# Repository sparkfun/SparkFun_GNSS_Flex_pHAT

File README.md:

SparkFun GNSS Flex pHAT
========================================

[*SparkFun GNSS Flex pHAT (GPS-28137)*](https://www.sparkfun.com/sparkfun-gnss-flex-phat.html)

The [SparkFun GNSS Flex pHAT](https://www.sparkfun.com/sparkfun-gnss-flex-phat.html) is a Raspberry Pi pHAT that functions as a *carrier board* for our SparkPNT GNSS Flex modules. With pre-soldered headers, no soldering is required to stack the pHAT on the headers of a Raspberry Pi, NVIDIA Jetson Nano, Google Coral, or other single-board computer with a similar 40-pin header.

The GNSS Flex pHAT also comes populated with two sets of 2x10 pin, 2mm pitch male headers for attaching a GNSS Flex module. With these headers, the GNSS Flex system is designed to be modular so that boards are pin-compatible for upgrades and can be easily swapped for repairs. Depending on the capabilities of the GNSS Flex module that is connected, these pins will breakout the USB, UART (x4), I<sup>2</sup>C, and SD card interfaces for the GNSS receiver along with any PPS or event signals, using a standardized pin out.

> [!NOTE]
> By default, we use the Raspberry Pi's primary serial bus *(i.e. **TX:** `GPIO14`/Pin `8`; **RX:** `GPIO15`/Pin `9`)* to communicate with the GNSS receiver of the SparkPNT GNSS Flex module. However, users can also utilize any of the other interfaces.

> [!IMPORTANT]
> Depending on the GNSS Flex module, this product will likely require an external antenna:
>
> - Be sure to check out the hookup guide for more information on the GNSS Flex module.
> - Users can also find [GNSS Antennas](https://www.sparkfun.com/gnss/gnss-antennas.html) in our catalog.
>
> Users will have two options for connecting an external GNSS antenna to their GNSS receiver.
>
> - The GNSS Flex modules will usually come with a U.FL connector for external antenna.
> - For a sturdier connection, an SMA connector is available on the SparkFun GNSS Flex pHAT that is bridged to an U.FL connector. Users simply need to jumper the U.FL connectors on both the SparkPNT GNSS Flex module and SparkFun GNSS Flex pHAT with a short U.FL cable.

> [!TIP]
> The SparkFun GNSS Flex pHAT has been tested and verified on the following platforms:
> - [Raspberry Pi](https://www.sparkfun.com/development-boards/single-board-computers/raspberry-pi/raspberry-pi-boards.html): 3B, 3B+, 3A+, Zero 2W, 4B, 5B
> - [NVidia Jetson Orin Nano](https://www.sparkfun.com/nvidia-jetson-orin-nano-developer-kit.html)

Documentation
--------------
- **[Hookup Guide (mkdocs)](http://docs.sparkfun.com/SparkFun_GNSS_Flex_System/)** - A hookup guide for the entire ecosystem of SparkFun GNSS Flex carrier boards and SparkPNT GNSS Flex modules, hosted by GitHub pages.<br>

Repository Contents
-------------------
- **[/docs](/docs/)** - Online documentation files
  - [/assets](/docs/assets/) - Assets files
    - [/3d_model](/docs/assets/3d_model/) - Files for the 3D models
      - [/3D CAD Model](/docs/assets/3d_model/cad_model.step) (.step)
    - [/board_files](/docs/assets/board_files/) - Files for the product design
      - [KiCad Design Files](/docs/assets/board_files/kicad_files.zip) (.zip)
      - [Schematic](/docs/assets/board_files/schematic.pdf) (.pdf)
      - [Dimensions](/docs/assets/board_files/dimensions.pdf) (.pdf)
    - [/component_documentation](/docs/assets/component_documentation/) - Datasheets for hardware components
    - [/img/hookup_guide/](/docs/assets/img/hookup_guide/) - Images for hookup guide documentation
- **[/Hardware](/Hardware/)** - Hardware design files (.brd, .sch)
  - **[/Production](/Production/)** - Production files

Product Variants
----------------
GNSS Flex *Carrier* Boards:
- [GPS-28962](https://www.sparkfun.com/sparkfun-gnss-flex-breakout.html) - GNSS Flex Breakout
- [GPS-28137](https://www.sparkfun.com/sparkfun-gnss-flex-phat.html) - GNSS Flex pHAT *(only)*

- GNSS Flex pHAT Kits:
  - pHAT + GNSS Module *(only)*:
    - [GPS-28766](https://www.sparkfun.com/sparkfun-gnss-flex-phat-mosaic-x5.html) - w/ the Septentrio mosaic-X5 GNSS Flex module
    - [GPS-28929](https://www.sparkfun.com/sparkfun-gnss-flex-phat-lg290p.html) - w/ the Quectel LG290P GNSS Flex module
    - [GPS-29491](https://www.sparkfun.com/sparkfun-gnss-flex-phat-dan-f10n.html) - w/ the u-blox DAN-F10N GNSS Flex module
    - [GPS-29887](https://www.sparkfun.com/sparkfun-gnss-flex-phat-zed-x20p.html) - w/ the u-blox ZED-X20P GNSS Flex module
    - [GPS-29890](https://www.sparkfun.com/sparkfun-gnss-flex-phat-lg580p.html) - w/ the Quectel LG580P GNSS Flex module
  - pHAT + GNSS Module w/ IMU:
    - [GPS-29891](https://www.sparkfun.com/sparkfun-gnss-flex-phat-lg290p-im19-imu.html) - w/ the Quectel LG290P GNSS Flex module + IM19 IMU
    - [GPS-29888](https://www.sparkfun.com/sparkfun-gnss-flex-phat-zed-x20p-im19-imu.html) - w/ the u-blox ZED-X20P GNSS Flex module + IM19 IMU

Version History
---------------
- [v01](https://github.com/sparkfun/SparkFun_GNSS_Flex_pHAT/releases/tag/v01) - Initial Release
- [v02](https://github.com/sparkfun/SparkFun_GNSS_Flex_pHAT/releases/tag/v02) - Adds DAN-F10N GNSS Flex module
- [v03](https://github.com/sparkfun/SparkFun_GNSS_Flex_pHAT/releases/tag/v03) - Adds LG290P and ZED-X20P GNSS Flex modules w/ optional IM19 IMU
- [v04](https://github.com/sparkfun/SparkFun_GNSS_Flex_pHAT/releases/tag/v04) - Update docs and link GNSS Flex breakout board
- [v10](https://github.com/sparkfun/SparkFun_GNSS_Flex_pHAT/releases/tag/v10) - Refactored the 3D model for new color adjustment script and linked the LG580P GNSS Flex module

License Information
-------------------

This product is ***open source***!

Please review the [`LICENSE.md`](./LICENSE.md) file for license information.

If you have any questions or concerns about licensing, please contact technical support on our [SparkFun forums](https://community.sparkpnt.com).

Distributed as-is; no warranty is given.

- Your friends at SparkFun.

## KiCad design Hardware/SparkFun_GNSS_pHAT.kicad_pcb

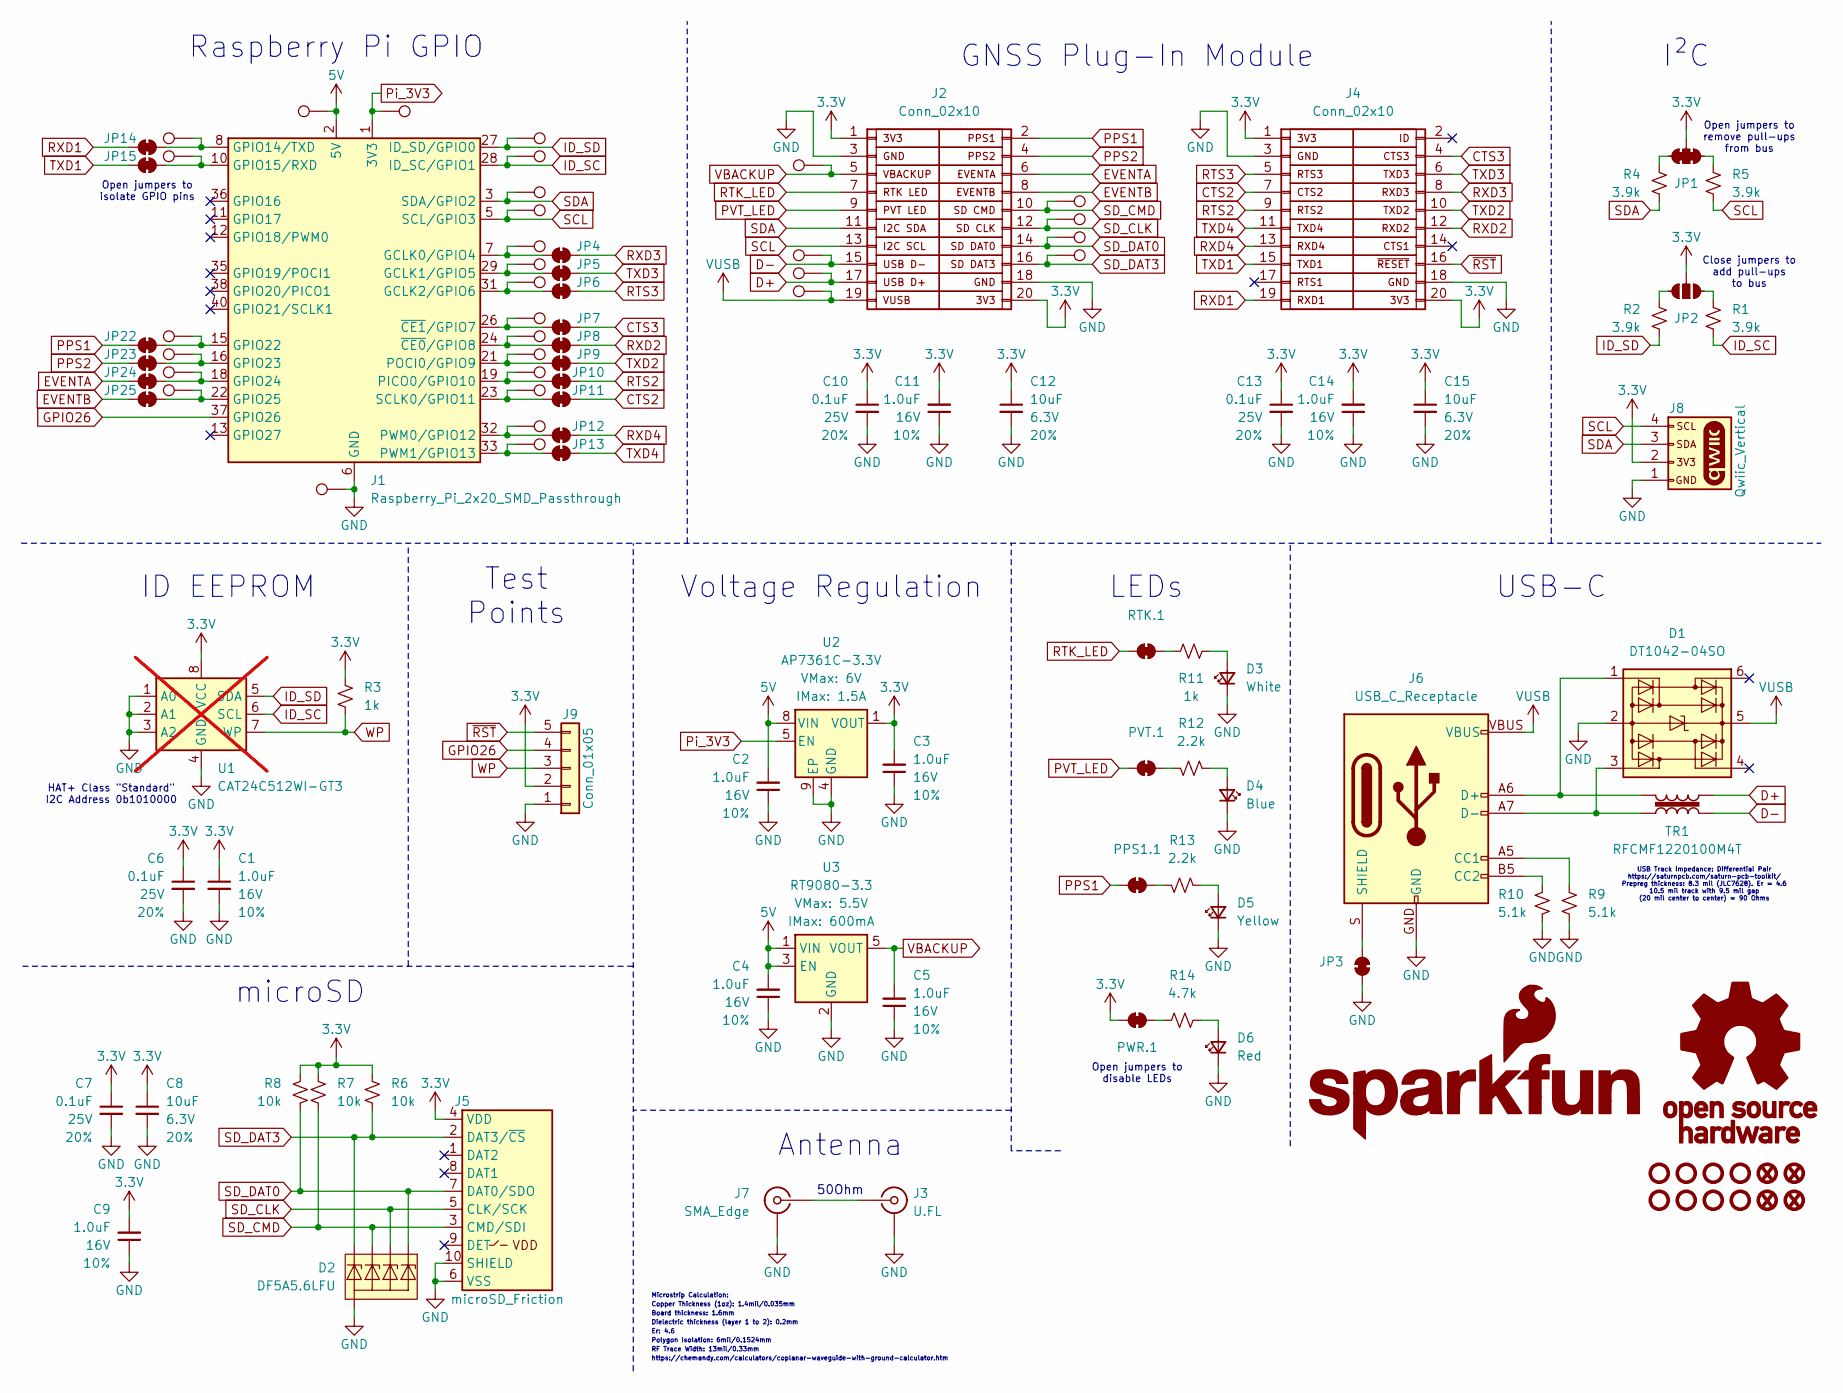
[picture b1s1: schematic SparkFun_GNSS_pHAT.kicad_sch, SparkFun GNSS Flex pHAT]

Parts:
C1, C2, C3, C4, C5, C9, C11, C14: 1.0uF; C_0603_1608Metric; Voltage 16V; Tolerance 10%
C6, C7, C10, C13: 0.1uF; C_0603_1608Metric; Voltage 25V; Tolerance 20%
C8, C12, C15: 10uF; C_0603_1608Metric; Voltage 6.3V; Tolerance 20%
D1: DT1042-04SO; SOT23-6
D2: DF5A5.6LFU; SOT-353
D3: White; LED_0603_1608Metric_White
D4: Blue; LED_0603_1608Metric_Blue
D5: Yellow; LED_0603_1608Metric_Yellow
D6: Red; LED_0603_1608Metric_Red
FID1, FID2, FID3, FID4: Fiducial_0.5mm; Fiducial_0.5mm_Mask1mm
G1: SparkFun_Logo
G3: OSHW_Logo; Creative_Commons_License
J1: Raspberry_Pi_2x20_SMD_Passthrough; Raspberry_Pi_Shield_Top_Entry_No_Mounting_Holes
J2, J4: Conn_02x10; 2x10_2.0mm_Male_Pins_Vertical_SMD_Pegs
J3: U.FL
J5: microSD_Friction; microSD_Friction_Fit_Common
J6: USB_C_Receptacle; USB-C_16
J7: SMA_Edge
J8: Qwiic_Vertical; JST_SMD_1.0mm-4_Vertical_Black
J9: Conn_01x05; 1x05
JP1: Jumper_3_NC-2_Trace
JP2: Jumper_3_NO
JP3, JP4, JP5, JP6, JP7, JP8, JP9, JP10, JP11, JP12, JP13, JP14, JP15, JP22, JP23, JP24, JP25: Jumper_2_NC_Trace
PPS1.1: Jumper_2_NC_Trace
PVT.1: Jumper_2_NC_Trace
PWR.1: Jumper_2_NC_Trace
R1, R2, R4, R5: 3.9k; R_0603_1608Metric
R3, R11: 1k; R_0603_1608Metric
R6, R7, R8: 10k; R_0603_1608Metric
R9, R10: 5.1k; R_0603_1608Metric
R12, R13: 2.2k; R_0603_1608Metric
R14: 4.7k; R_0603_1608Metric
RTK.1: Jumper_2_NC_Trace
ST1, ST2, ST3, ST4: Standoff
ST5, ST6, ST7, ST8: Standoff; Standoff_Hole-2.75mm_Clearance-1.625mm
TP1, TP2, TP3, TP4, TP5, TP6, TP7, TP8, TP9, TP10, TP11, TP12, TP13, TP14, TP15, TP16, TP17, TP18, TP19, TP20, TP21, TP22, TP23, TP24, TP25, TP26, TP27, TP28, TP29, TP30, TP31: 1.25mm; TestPoint-1.25mm
TR1: RFCMF1220100M4T
U1: CAT24C512WI-GT3; SO-8; not fitted
U2: AP7361C-3.3V; UDFN-8
U3: RT9080-3.3; SOT23-5

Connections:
3.3V: C1.1, C3.2, C6.1, C7.1, C8.1, C9.2, C10.1, C11.2, C12.1, C13.1, C14.2, C15.1, J2.1, J2.20, J4.1, J4.20, J5.4 (VDD), J8.2, J9.2, JP1.2 (B), JP2.2 (B), PWR.1.2 (B), R3.2, R6.2, R7.2, R8.2, U1.8 (VCC), U2.1 (VOUT)
5V: C2.2, C4.2, J1.2 (5V), J1.4 (5V), TP22.1, U2.8 (VIN), U3.1 (VIN), U3.3 (EN)
CTS2: J4.7, JP11.2 (B)
CTS3: J4.4, JP7.2 (B)
D+: J2.17, TP25.1, TR1.4
D-: J2.15, TP24.1, TR1.2
EVENTA: J2.6, JP24.1 (A)
EVENTB: J2.8, JP25.1 (A)
GND: C1.2, C2.1, C3.1, C4.1, C5.1, C6.2, C7.2, C8.2, C9.1, C10.2, C11.1, C12.2, C13.2, C14.1, C15.2, D1.2 (GND), D2.2 (A), D3.1 (K), D4.1 (K), D5.1 (K), D6.1 (K), J1.6 (GND), J1.9 (GND), J1.14 (GND), J1.20 (GND), J1.25 (GND), J1.30 (GND), J1.34 (GND), J1.39 (GND), J2.3, J2.18, J3.2 (Ext), J4.3, J4.18, J5.6 (VSS), J5.10 (SHIELD), J6.GND, J7.2 (Ext), J8.1, J9.1, JP3.1 (A), R9.1, R10.1, TP31.1, U1.1 (A0), U1.2 (A1), U1.3 (A2), U1.4 (GND), U2.4 (GND), U2.9 (EP), U3.2 (GND)
GPIO26: J1.37 (GPIO26), J9.4
ID_SC: J1.28 (ID_SC/GPIO1), R1.1, TP2.1, U1.6 (SCL)
ID_SD: J1.27 (ID_SD/GPIO0), R2.1, TP1.1, U1.5 (SDA)
unnamed: D1.1 (I/O1), J6.A6 (D+), J6.B6 (D+), TR1.3
unnamed: D1.3 (I/O2), J6.A7 (D-), J6.B7 (D-), TR1.1
unnamed: D3.2 (A), R11.1
unnamed: D4.2 (A), R12.1
unnamed: D5.2 (A), R13.1
unnamed: D6.2 (A), R14.2
unnamed: J1.7 (GCLK0/GPIO4), JP4.1 (A), TP5.1
unnamed: J1.29 (GCLK1/GPIO5), JP5.1 (A), TP6.1
unnamed: J1.31 (GCLK2/GPIO6), JP6.1 (A), TP7.1
unnamed: J1.8 (GPIO14/TXD), JP14.2 (B), TP15.1
unnamed: J1.10 (GPIO15/RXD), JP15.2 (B), TP16.1
unnamed: J1.15 (GPIO22), JP22.2 (B), TP17.1
unnamed: J1.16 (GPIO23), JP23.2 (B), TP18.1
unnamed: J1.18 (GPIO24), JP24.2 (B), TP19.1
unnamed: J1.22 (GPIO25), JP25.2 (B), TP20.1
unnamed: J1.19 (PICO0/GPIO10), JP10.1 (A), TP11.1
unnamed: J1.21 (POCI0/GPIO9), JP9.1 (A), TP10.1
unnamed: J1.32 (PWM0/GPIO12), JP12.1 (A), TP13.1
unnamed: J1.33 (PWM1/GPIO13), JP13.1 (A), TP14.1
unnamed: J1.23 (SCLK0/GPIO11), JP11.1 (A), TP12.1
unnamed: J1.24 (~CE0/GPIO8), JP8.1 (A), TP9.1
unnamed: J1.26 (~CE1/GPIO7), JP7.1 (A), TP8.1
unnamed: J3.1 (In), J7.1 (In)
unnamed: J6.A5 (CC1), R9.2
unnamed: J6.B5 (CC2), R10.2
unnamed: J6.S (SHIELD), JP3.2 (B)
unnamed: JP1.1 (A), R5.2
unnamed: JP1.3 (C), R4.2
unnamed: JP2.1 (A), R1.2
unnamed: JP2.3 (C), R2.2
unnamed: PPS1.1.2 (B), R13.2
unnamed: PVT.1.2 (B), R12.2
unnamed: PWR.1.1 (A), R14.1
unnamed: R11.2, RTK.1.2 (B)
PPS1: J2.2, JP22.1 (A), PPS1.1.1 (A)
PPS2: J2.4, JP23.1 (A)
PVT_LED: J2.9, PVT.1.1 (A)
Pi_3V3: J1.1 (3V3), J1.17 (3V3), TP23.1, U2.5 (EN)
RTK_LED: J2.7, RTK.1.1 (A)
RTS2: J4.9, JP10.2 (B)
RTS3: J4.5, JP6.2 (B)
RXD1: J4.19, JP14.1 (A)
RXD2: J4.12, JP8.2 (B)
RXD3: J4.8, JP4.2 (B)
RXD4: J4.13, JP12.2 (B)
SCL: J1.5 (SCL/GPIO3), J2.13, J8.4, R5.1, TP4.1
SDA: J1.3 (SDA/GPIO2), J2.11, J8.3, R4.1, TP3.1
SD_CLK: D2.3 (K2), J2.12, J5.5 (CLK/SCK), TP29.1
SD_CMD: D2.4 (K3), J2.10, J5.3 (CMD/SDI), R7.1, TP30.1
SD_DAT0: D2.1 (K1), J2.14, J5.7 (DAT0/SDO), R8.1, TP28.1
SD_DAT3: D2.5 (K4), J2.16, J5.2 (DAT3/~CS), R6.1, TP27.1
TXD1: J4.15, JP15.1 (A)
TXD2: J4.10, JP9.2 (B)
TXD3: J4.6, JP5.2 (B)
TXD4: J4.11, JP13.2 (B)
VBACKUP: C5.2, J2.5, TP21.1, U3.5 (VOUT)
VUSB: D1.5 (VCC), J2.19, J6.VBUS, TP26.1
WP: J9.3, R3.1, U1.7 (WP)
~RST: J4.16, J9.5

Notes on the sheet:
Er: 4.6
50Ohm
Raspberry Pi GPIO
Board thickness: 1.6mm
https://chemandy.com/calculators/coplanar-waveguide-with-ground-calculator.htm
Close jumpers to add pull-ups to bus
Open jumpers to remove pull-ups from bus
RF Trace Width: 13mil/0.33mm
Test Points
Polygon Isolation: 6mil/0.1524mm
microSD
Antenna
Open jumpers to disable LEDs
Dielectric thickness (layer 1 to 2): 0.2mm
LEDs
Voltage Regulation
USB Track Impedance: Differential Pair https://saturnpcb.com/saturn-pcb-toolkit/ Prepreg thickness: 8.3 mil (JLC7628). Er = 4.6 10.5 mil track with 9.5 mil gap (20 mil center to center) = 90 Ohms
Open jumpers to isolate GPIO pins
ID EEPROM
HAT+ Class "Standard" I2C Address 0b1010000
GNSS Plug-In Module
Microstrip Calculation:
I²C
USB-C
Copper Thickness (1oz): 1.4mil/0.035mm

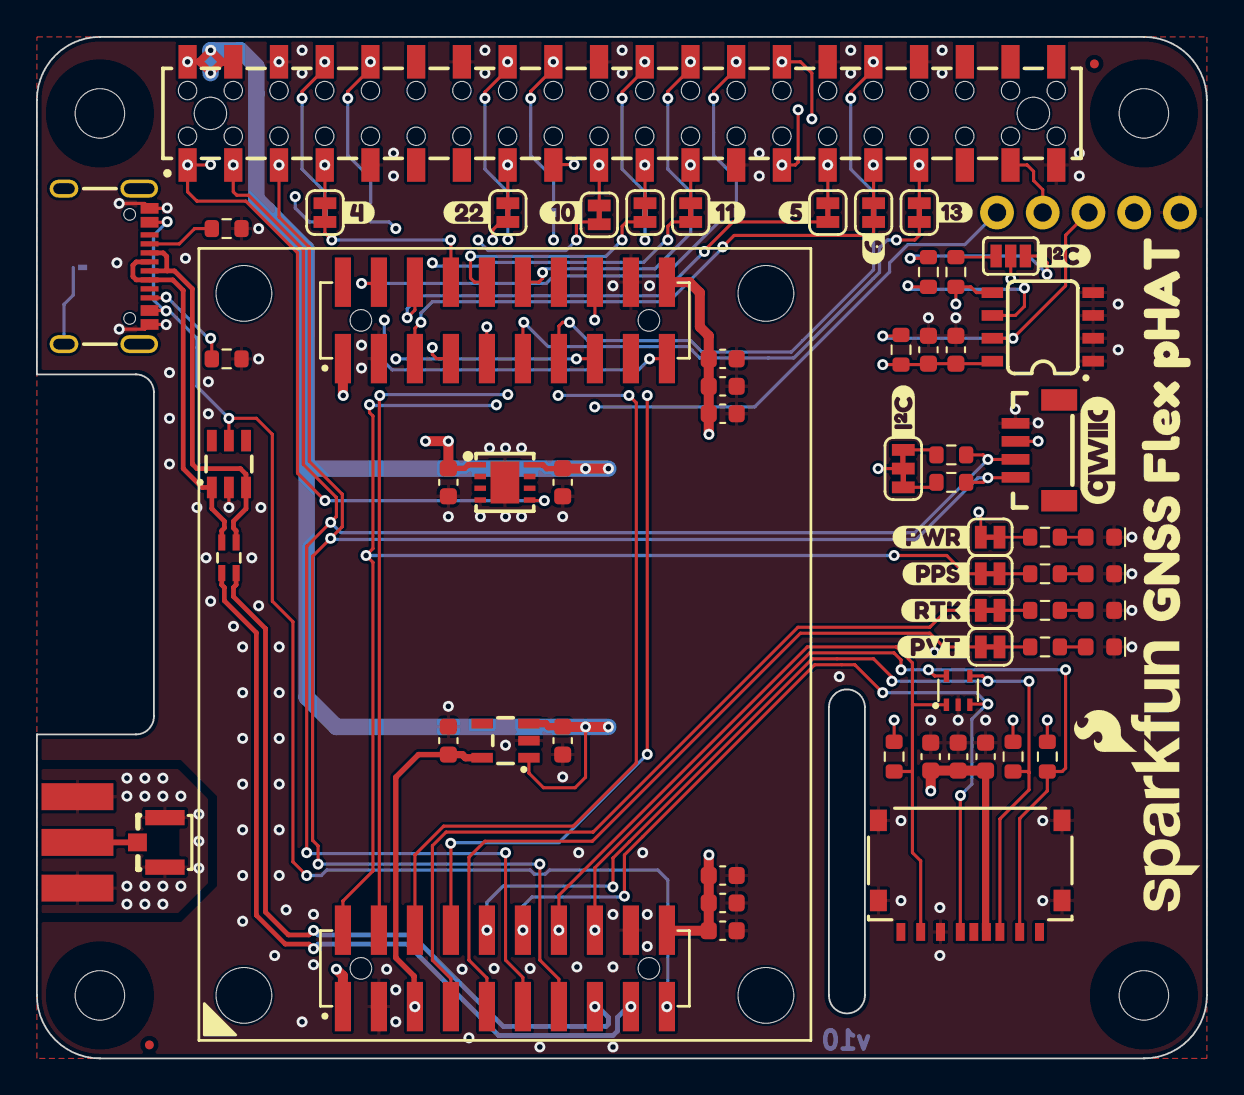
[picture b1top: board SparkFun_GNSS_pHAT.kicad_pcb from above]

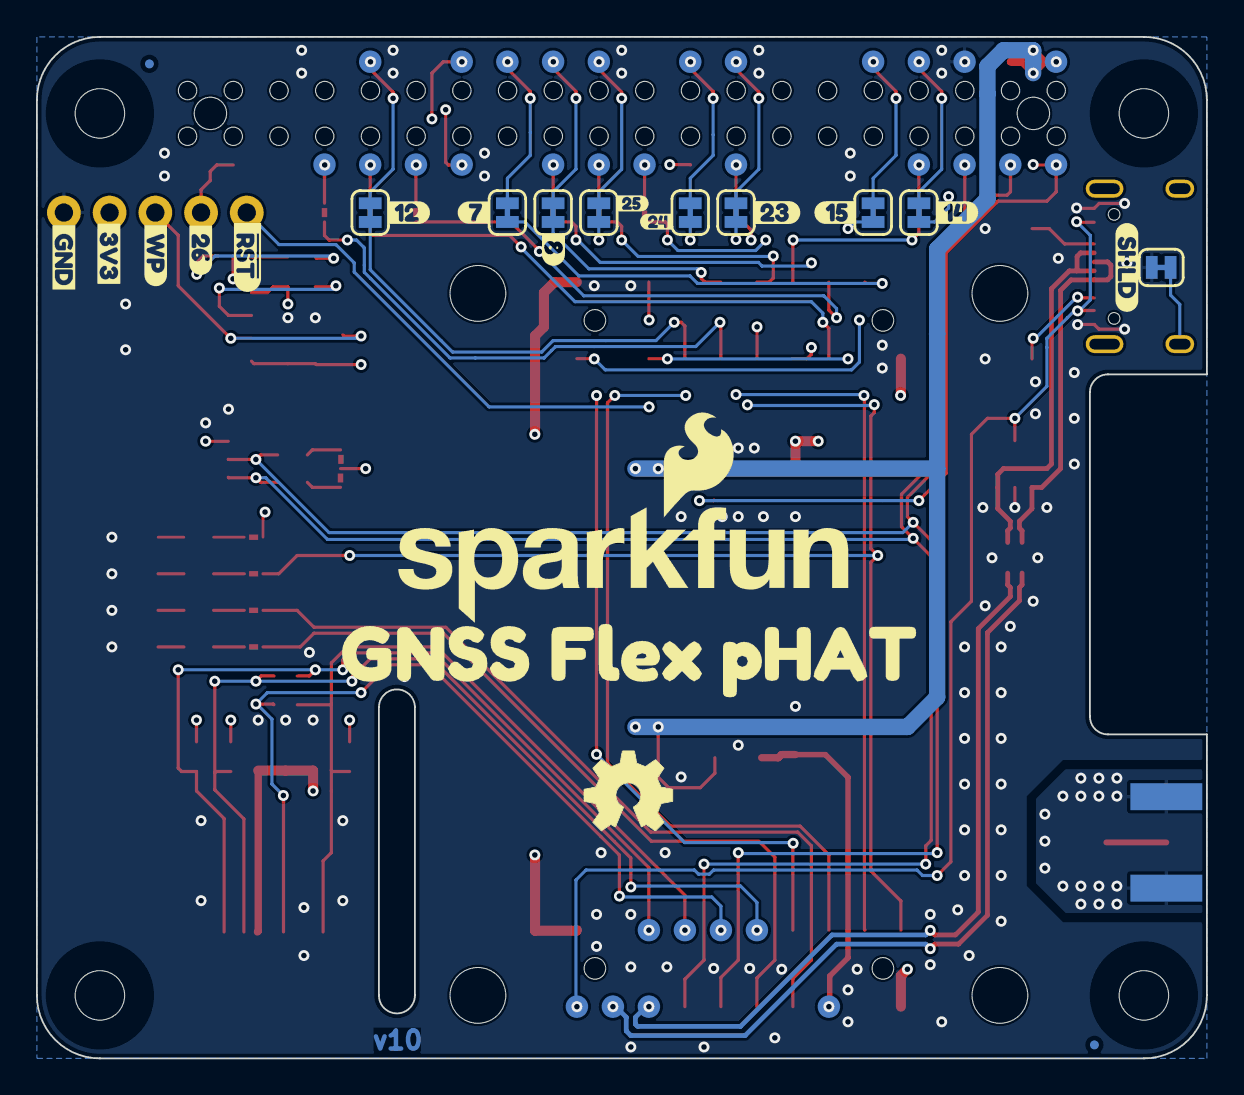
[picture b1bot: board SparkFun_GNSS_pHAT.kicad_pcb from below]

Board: 4 copper layers, 65.0 x 56.8 mm, 145 parts (58 on the bottom side), 71 nets.

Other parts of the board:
Ref**: Val**; OSHW_Logo_5mm
kibuzzard-67DC18B6: G***; kibuzzard-67DC18B6
kibuzzard-67DC1838: G***; kibuzzard-67DC1838
kibuzzard-678F8AD2: G***; kibuzzard-678F8AD2
kibuzzard-678F8D59: G***; kibuzzard-678F8D59
kibuzzard-678F8D86: G***; kibuzzard-678F8D86
kibuzzard-678F8DB2: G***; kibuzzard-678F8DB2
kibuzzard-678F8E11: G***; kibuzzard-678F8E11
kibuzzard-678F8E25: G***; kibuzzard-678F8E25
kibuzzard-678F8E41: G***; kibuzzard-678F8E41
kibuzzard-678F8E95: G***; kibuzzard-678F8E95
kibuzzard-678F8EB4: G***; kibuzzard-678F8EB4
kibuzzard-678F8ED3: G***; kibuzzard-678F8ED3
kibuzzard-678F8EED: G***; kibuzzard-678F8EED
kibuzzard-678F8F2B: G***; kibuzzard-678F8F2B
kibuzzard-678F8F11: G***; kibuzzard-678F8F11
kibuzzard-678F8F42: G***; kibuzzard-678F8F42
kibuzzard-678F92B8: G***; kibuzzard-678F92B8
kibuzzard-678F878F: G***; kibuzzard-678F878F
kibuzzard-678F893B, kibuzzard-678F893B#2: G***; kibuzzard-678F893B
kibuzzard-678F918F: G***; kibuzzard-678F918F
kibuzzard-678F8755: G***; kibuzzard-678F8755
kibuzzard-678F8777: G***; kibuzzard-678F8777
kibuzzard-67922E39: G***; kibuzzard-67922E39
kibuzzard-67922EA6: G***; kibuzzard-67922EA6
kibuzzard-67922FE7: G***; kibuzzard-67922FE7
kibuzzard-679237A8: G***; kibuzzard-679237A8
kibuzzard-679237B7: G***; kibuzzard-679237B7
kibuzzard-67923645: G***; kibuzzard-67923645

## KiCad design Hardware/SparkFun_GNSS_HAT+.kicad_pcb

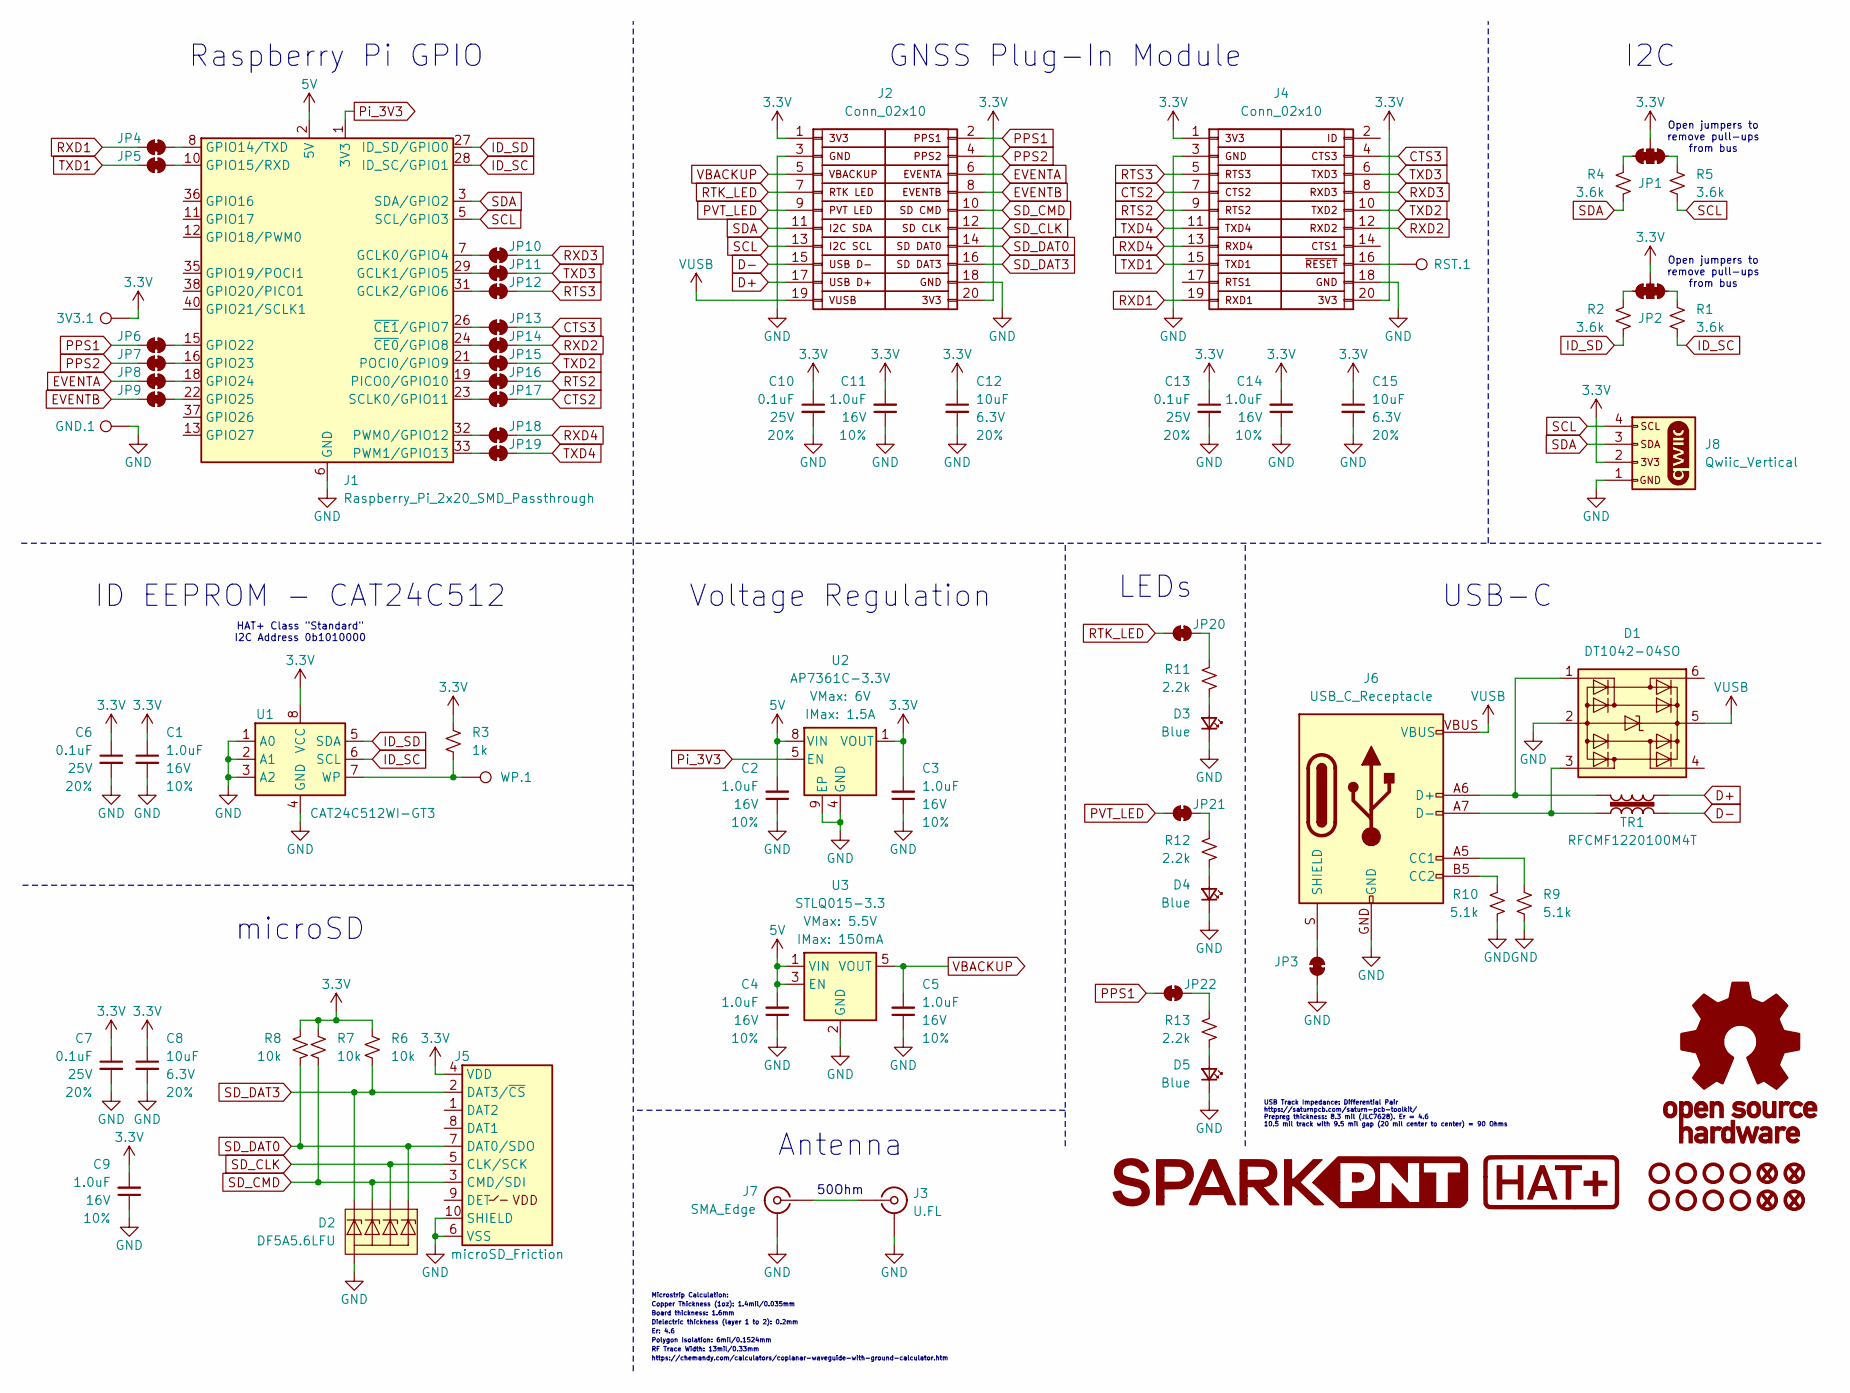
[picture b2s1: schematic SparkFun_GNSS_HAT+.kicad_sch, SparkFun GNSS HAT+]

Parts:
3V3.1: PTH; 1x01
C1, C2, C3, C4, C5, C9, C11, C14: 1.0uF; C_0603_1608Metric; Voltage 16V; Tolerance 10%
C6, C7, C10, C13: 0.1uF; C_0603_1608Metric; Voltage 25V; Tolerance 20%
C8, C12, C15: 10uF; C_0603_1608Metric; Voltage 6.3V; Tolerance 20%
D1: DT1042-04SO; SOT23-6
D2: DF5A5.6LFU; SOT-353
D3, D4, D5: Blue; LED_0603_1608Metric_Blue
FID1, FID2, FID3, FID4: Fiducial_0.5mm; Fiducial_0.5mm_Mask1mm
G1: LOGO
G3: OSHW_Logo; Creative_Commons_License
GND.1: PTH; 1x01
J1: Raspberry_Pi_2x20_SMD_Passthrough; Raspberry_Pi_Shield_Top_Entry_No_Mounting_Holes
J2, J4: Conn_02x10; 2x10_2.0mm_Male_Pins_Vertical_SMD
J3: U.FL
J5: microSD_Friction; microSD_Friction_Fit_Common
J6: USB_C_Receptacle; USB-C_16
J7: SMA_Edge
J8: Qwiic_Vertical; JST_SMD_1.0mm-4_Vertical
JP1, JP2: Jumper_3_NC-2_Trace
JP3, JP4, JP5, JP6, JP7, JP8, JP9, JP10, JP11, JP12, JP13, JP14, JP15, JP16, JP17, JP18, JP19, JP20, JP21, JP22: Jumper_2_NC_Trace
R1, R2, R4, R5: 3.6k; R_0603_1608Metric
R3: 1k; R_0603_1608Metric
R6, R7, R8: 10k; R_0603_1608Metric
R9, R10: 5.1k; R_0603_1608Metric
R11, R12, R13: 2.2k; R_0603_1608Metric
RST.1: PTH; 1x01
ST1, ST2, ST3, ST4: Standoff
ST5, ST6, ST7, ST8: Standoff; Standoff_Raspberry-Pi_HAT+
TR1: RFCMF1220100M4T
U1: CAT24C512WI-GT3; SO-8
U2: AP7361C-3.3V; UDFN-8
U3: STLQ015-3.3; SOT23-5
WP.1: PTH; 1x01

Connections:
3.3V: 3V3.1.1, C1.1, C3.2, C6.1, C7.1, C8.1, C9.2, C10.1, C11.2, C12.1, C13.1, C14.2, C15.1, J2.1, J2.20 (Pin_2), J4.1, J4.20 (Pin_2), J5.4 (VDD), J8.2, JP1.2 (B), JP2.2 (B), R3.2, R6.2, R7.2, R8.2, U1.8 (VCC), U2.1 (VOUT)
5V: C2.2, C4.2, J1.2 (5V), J1.4 (5V), U2.8 (VIN), U3.1 (VIN), U3.3 (EN)
CTS2: J4.7, JP17.2 (B)
CTS3: J4.4, JP13.2 (B)
D+: J2.17 (Pin_1), TR1.4
D-: J2.15 (Pin_1), TR1.2
EVENTA: J2.6, JP8.1 (A)
EVENTB: J2.8, JP9.1 (A)
GND: C1.2, C2.1, C3.1, C4.1, C5.1, C6.2, C7.2, C8.2, C9.1, C10.2, C11.1, C12.2, C13.2, C14.1, C15.2, D1.2 (GND), D2.2 (A), D3.1 (K), D4.1 (K), D5.1 (K), GND.1.1, J1.6 (GND), J1.9 (GND), J1.14 (GND), J1.20 (GND), J1.25 (GND), J1.30 (GND), J1.34 (GND), J1.39 (GND), J2.3, J2.18 (Pin_2), J3.2 (Ext), J4.3, J4.18 (Pin_2), J5.6 (VSS), J5.10 (SHIELD), J6.GND, J7.2 (Ext), J8.1, JP3.1 (A), R9.1, R10.1, U1.1 (A0), U1.2 (A1), U1.3 (A2), U1.4 (GND), U2.4 (GND), U2.9 (EP), U3.2 (GND)
ID_SC: J1.28 (ID_SC/GPIO1), R1.1, U1.6 (SCL)
ID_SD: J1.27 (ID_SD/GPIO0), R2.1, U1.5 (SDA)
unnamed: D1.1 (I/O1), J6.A6 (D+), J6.B6 (D+), TR1.3
unnamed: D1.3 (I/O2), J6.A7 (D-), J6.B7 (D-), TR1.1
unnamed: D3.2 (A), R11.1
unnamed: D4.2 (A), R12.1
unnamed: D5.2 (A), R13.1
unnamed: J1.7 (GCLK0/GPIO4), JP10.1 (A)
unnamed: J1.29 (GCLK1/GPIO5), JP11.1 (A)
unnamed: J1.31 (GCLK2/GPIO6), JP12.1 (A)
unnamed: J1.8 (GPIO14/TXD), JP4.2 (B)
unnamed: J1.10 (GPIO15/RXD), JP5.2 (B)
unnamed: J1.15 (GPIO22), JP6.2 (B)
unnamed: J1.16 (GPIO23), JP7.2 (B)
unnamed: J1.18 (GPIO24), JP8.2 (B)
unnamed: J1.22 (GPIO25), JP9.2 (B)
unnamed: J1.19 (PICO0/GPIO10), JP16.1 (A)
unnamed: J1.21 (POCI0/GPIO9), JP15.1 (A)
unnamed: J1.32 (PWM0/GPIO12), JP18.1 (A)
unnamed: J1.33 (PWM1/GPIO13), JP19.1 (A)
unnamed: J1.23 (SCLK0/GPIO11), JP17.1 (A)
unnamed: J1.24 (~CE0/GPIO8), JP14.1 (A)
unnamed: J1.26 (~CE1/GPIO7), JP13.1 (A)
unnamed: J3.1 (In), J7.1 (In)
unnamed: J4.16 (Pin_2), RST.1.1
unnamed: J6.A5 (CC1), R9.2
unnamed: J6.B5 (CC2), R10.2
unnamed: J6.S (SHIELD), JP3.2 (B)
unnamed: JP1.1 (A), R5.2
unnamed: JP1.3 (C), R4.2
unnamed: JP2.1 (A), R1.2
unnamed: JP2.3 (C), R2.2
unnamed: JP20.2 (B), R11.2
unnamed: JP21.2 (B), R12.2
unnamed: JP22.2 (B), R13.2
unnamed: R3.1, U1.7 (WP), WP.1.1
PPS1: J2.2, JP6.1 (A), JP22.1 (A)
PPS2: J2.4, JP7.1 (A)
PVT_LED: J2.9, JP21.1 (A)
Pi_3V3: J1.1 (3V3), J1.17 (3V3), U2.5 (EN)
RTK_LED: J2.7, JP20.1 (A)
RTS2: J4.9, JP16.2 (B)
RTS3: J4.5, JP12.2 (B)
RXD1: J4.19 (Pin_1), JP4.1 (A)
RXD2: J4.12 (Pin_2), JP14.2 (B)
RXD3: J4.8, JP10.2 (B)
RXD4: J4.13 (Pin_1), JP18.2 (B)
SCL: J1.5 (SCL/GPIO3), J2.13 (Pin_1), J8.4, R5.1
SDA: J1.3 (SDA/GPIO2), J2.11 (Pin_1), J8.3, R4.1
SD_CLK: D2.3 (K2), J2.12 (Pin_2), J5.5 (CLK/SCK)
SD_CMD: D2.4 (K3), J2.10, J5.3 (CMD/SDI), R7.1
SD_DAT0: D2.1 (K1), J2.14 (Pin_2), J5.7 (DAT0/SDO), R8.1
SD_DAT3: D2.5 (K4), J2.16 (Pin_2), J5.2 (DAT3/~CS), R6.1
TXD1: J4.15 (Pin_1), JP5.1 (A)
TXD2: J4.10, JP15.2 (B)
TXD3: J4.6, JP11.2 (B)
TXD4: J4.11 (Pin_1), JP19.2 (B)
VBACKUP: C5.2, J2.5, U3.5 (VOUT)
VUSB: D1.5 (VCC), J2.19 (Pin_1), J6.VBUS

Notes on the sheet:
Er: 4.6
50Ohm
Raspberry Pi GPIO
Board thickness: 1.6mm
https://chemandy.com/calculators/coplanar-waveguide-with-ground-calculator.htm
Open jumpers to remove pull-ups from bus
RF Trace Width: 13mil/0.33mm
Polygon Isolation: 6mil/0.1524mm
microSD
Antenna
Dielectric thickness (layer 1 to 2): 0.2mm
LEDs
Voltage Regulation
USB Track Impedance: Differential Pair https://saturnpcb.com/saturn-pcb-toolkit/ Prepreg thickness: 8.3 mil (JLC7628). Er = 4.6 10.5 mil track with 9.5 mil gap (20 mil center to center) = 90 Ohms
ID EEPROM - CAT24C512
HAT+ Class "Standard" I2C Address 0b1010000
GNSS Plug-In Module
Microstrip Calculation:
I2C
USB-C
Copper Thickness (1oz): 1.4mil/0.035mm

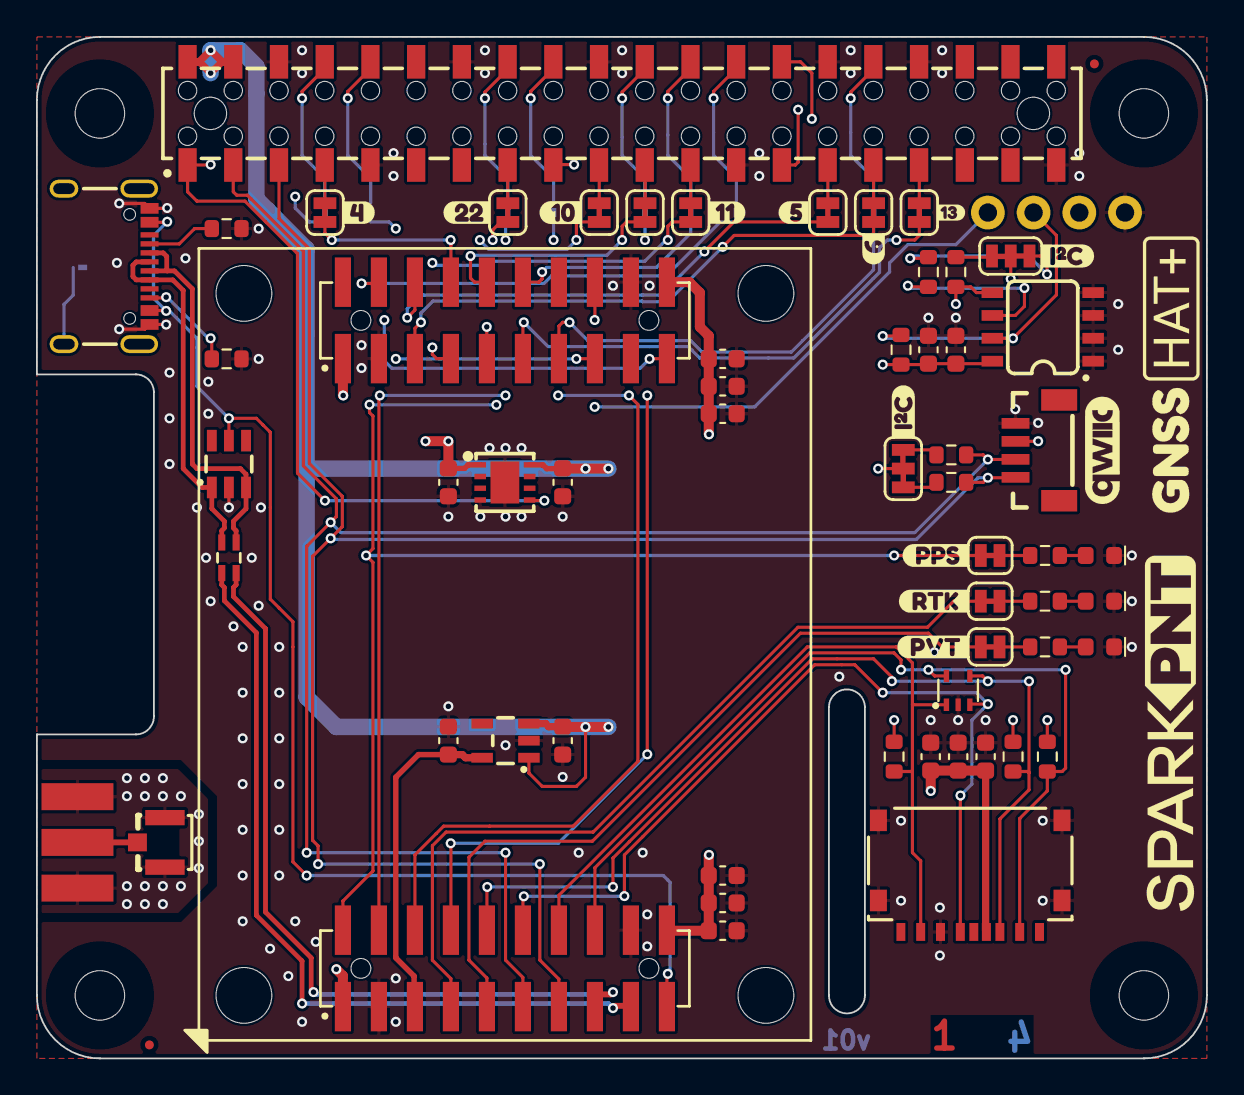
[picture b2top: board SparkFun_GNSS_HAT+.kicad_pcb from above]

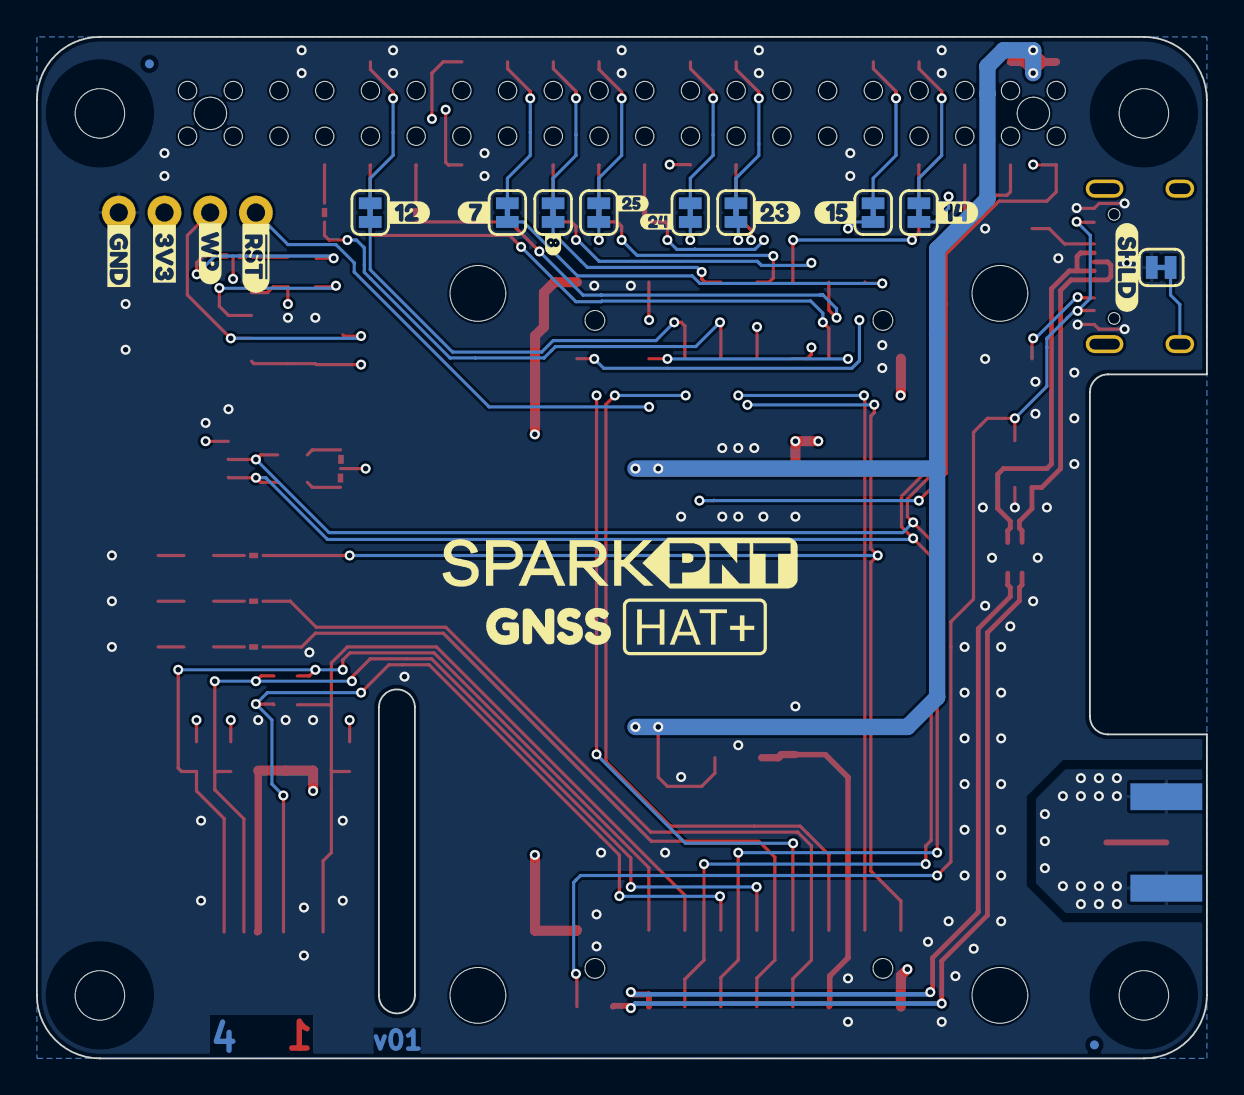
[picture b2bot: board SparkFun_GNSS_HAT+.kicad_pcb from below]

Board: 4 copper layers, 65.0 x 56.8 mm, 111 parts (25 on the bottom side), 68 nets.

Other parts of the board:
kibuzzard-678F8AD2: G***; kibuzzard-678F8AD2
kibuzzard-678F8D59: G***; kibuzzard-678F8D59
kibuzzard-678F8D86: G***; kibuzzard-678F8D86
kibuzzard-678F8DB2: G***; kibuzzard-678F8DB2
kibuzzard-678F8DFF: G***; kibuzzard-678F8DFF
kibuzzard-678F8E11: G***; kibuzzard-678F8E11
kibuzzard-678F8E25: G***; kibuzzard-678F8E25
kibuzzard-678F8E41: G***; kibuzzard-678F8E41
kibuzzard-678F8E95: G***; kibuzzard-678F8E95
kibuzzard-678F8EB4: G***; kibuzzard-678F8EB4
kibuzzard-678F8ED3: G***; kibuzzard-678F8ED3
kibuzzard-678F8EED: G***; kibuzzard-678F8EED
kibuzzard-678F8F2B: G***; kibuzzard-678F8F2B
kibuzzard-678F8F11: G***; kibuzzard-678F8F11
kibuzzard-678F8F42: G***; kibuzzard-678F8F42
kibuzzard-678F8FC6: G***; kibuzzard-678F8FC6
kibuzzard-678F89CB: G***; kibuzzard-678F89CB
kibuzzard-678F89E9: G***; kibuzzard-678F89E9
kibuzzard-678F92B8: G***; kibuzzard-678F92B8
kibuzzard-678F852F, kibuzzard-678F852F#2: G***; kibuzzard-678F852F
kibuzzard-678F878F: G***; kibuzzard-678F878F
kibuzzard-678F893B, kibuzzard-678F893B#2: G***; kibuzzard-678F893B
kibuzzard-678F918F: G***; kibuzzard-678F918F
kibuzzard-678F8755: G***; kibuzzard-678F8755
kibuzzard-678F8777: G***; kibuzzard-678F8777

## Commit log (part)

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2025-01-16 Very WIP
2025-01-17 More WIP
2025-01-21 Routed
2025-01-21 Panelized
2025-01-22 Change dimensions to mm
2025-01-23 Change name to GNSS pHAT
2025-01-23 pHAT routed and panelized
2025-01-23 Updates to match KiCad lib after #171
2025-01-27 Increase via size
2025-01-29 pHAT updated after review
2025-01-30 Update standoffs. Change panel to 2x2
2025-01-31 Update RPi passthrough connector PROD_ID
2025-01-31 Change I2C pull-ups to 3.9K RES-08701
2025-03-20 v10 - update connectors and silk
2025-03-20 v10. Rename to Flex pHAT. Update 2x10 connectors and silk.
    No paste changes
    The only PnP changes are the 2x10 connector type. PnP coordinates are all the same.
2025-04-29 Add/update template files
2025-05-20 Add README
2025-05-20 Initial Draft - Docs
2025-05-20 Update README.md
    Fix merge errors
    Remove "print view" link
2025-05-20 Update Docs
2025-05-20 Add documentation
2025-05-20 Fix repo link
2025-05-20 Replace center tag
    Replace the use of `<center>` tag for deprecation, as described in issue: https://github.com/squidfunk/mkdocs-material/issues/8163
2025-05-20 Add UART highlight colors
2025-05-20 Add login shell tip
2025-05-20 Add note about PyGPSClient on desktop
2025-05-20 Add PyGPSClient disconnect tip
2025-05-20 Add UART tips and how-to enable the additional ports
2025-05-20 Correct single quotes
2025-05-21 Update resources.md
    Add product showcase video
    Add product link
2025-05-21 Qwiic connect system
    Add standard info for Qwiic connect system
2025-05-21 Update mkdocs.yml
    Add repo and uri configuration
    - Edit button link is still wrong, but better than redirecting to incorrect repo
2025-05-21 Add USB interface
2025-05-21 Remove color adjustment script
    Automatically built into documentation
2025-05-21 Update hardware_overview.md
    Add product link
    Add hookup guide banner
2025-05-21 Delete software-pygpsclient.md
    Not used
2025-05-21 Update software_overview.md
    Swap order
2025-05-21 Fix video containers
    For removed center tag
2025-05-22 Update kicad_files.zip
    Add project file
2025-08-20 Add LDO Datasheets
    Add datasheets for voltage regulators
2025-08-20 Add images
    - Template for board layout
    - Breakout pins (EEPROM - not used)
2025-08-20 Link U.FL Cable
    Add product link for 50mm U.FL cable
2025-08-20 Update docs
    Fix Heading
    Fix Spacing
    Add width for QR codes
    Fix link
    Add link back to all GNSS Flex modules
2025-08-21 Add DAN-F10N
    Add links to DAN-F10N kit
2025-08-21 Update version history in README
    Corrected the initial release version from v10 to v01 and added v02 with details about the DAN-F10N GNSS Flex module.
2025-09-10 Update .gitignore
    Remove leftover merge conflict markers
    Consolidate duplicate entries
2025-09-10 Remove cache files
2025-09-10 Add LG290P + ZED-X20P w/ optional IM19
    Adds product links for new GNSS Flex modules
2025-09-12 Update KiCAD files
    Update the file path to the 3D model of the RF choke's footprint
    Remove ignored file type
2025-09-15 Replace <center> and <sup> tags
    Update <center> tags to conform to HTML5 standards
    Replace <sup> tag with markdown notation
2025-09-15 Update hardware_assembly.md
    Update instructions for connecting an external antenna
2025-09-15 Update README.md
    Add product links
2025-09-15 Update software_overview.md
    Adds instructions for enabling the I2C interface
    Add example for configuring the UART interface on a Pi 5
2025-09-18 Update docs
    Fix grammar
    Fix link
    Fix table
    Adds instructions for connecting Qwiic devices
2025-09-18 Add GNSS Flex Breakout
    Adds product link to GNSS Flex Breakout board
    Adds new release version updates
2025-09-18 Add links for Flex board pages
    Links to main carrier board and modules pages
2025-09-18 Update hardware_assembly.md
    Small formatting change to match GNSS Flex breakout board
2025-10-10 Update 3D model
    Refactored the 3D model for all the GNSS Flex boards to a new standardization
    Eliminated the manual adjustments required for any new 3D models
    - Modified the old models, so any new models can be adopted without any changes after they have been optimized
2025-10-10 Add LG580P GNSS Flex module
    Added links for the LG580P GNSS Flex module
    Updated version history to include v10 release notes
2026-02-25 Docs - Tech Assist Update
    Removed links to technical assistance webpage (404 retail site)
    - Removed or relocated???

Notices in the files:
parts and their libraries:
https://creativecommons.org/licenses/by-sa/4.0
Released under the Creative Commons Attribution Share-Alike 4.0 License
